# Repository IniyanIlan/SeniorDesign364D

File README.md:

# Tides of Treachery

# How to Run the Frontend
In the `src` directory, you can run:

### `npm start`

Runs the app in the development mode.\
Open [http://localhost:3000](http://localhost:3000) to view it in your browser.

The page will reload when you make changes.\
You may also see any lint errors in the console.

### `npm run build`

Builds the app for production to the `build` folder.\
It correctly bundles React in production mode and optimizes the build for the best performance.

The build is minified and the filenames include the hashes.\
Your app is ready to be deployed!

# How to Run the Backend

Split the terminal, and go to the `backend` directory.

Run this command:

### `python -m venv --system-site-packages venv`

This will create an environment with all the necessary dependencies for the application.

Next, run this command:

### `./venv/bin/activate`

This command will activate the virtual environment.

Lastly, run the backend application with this command:

### `python app.py`

# Navigate to the React Application

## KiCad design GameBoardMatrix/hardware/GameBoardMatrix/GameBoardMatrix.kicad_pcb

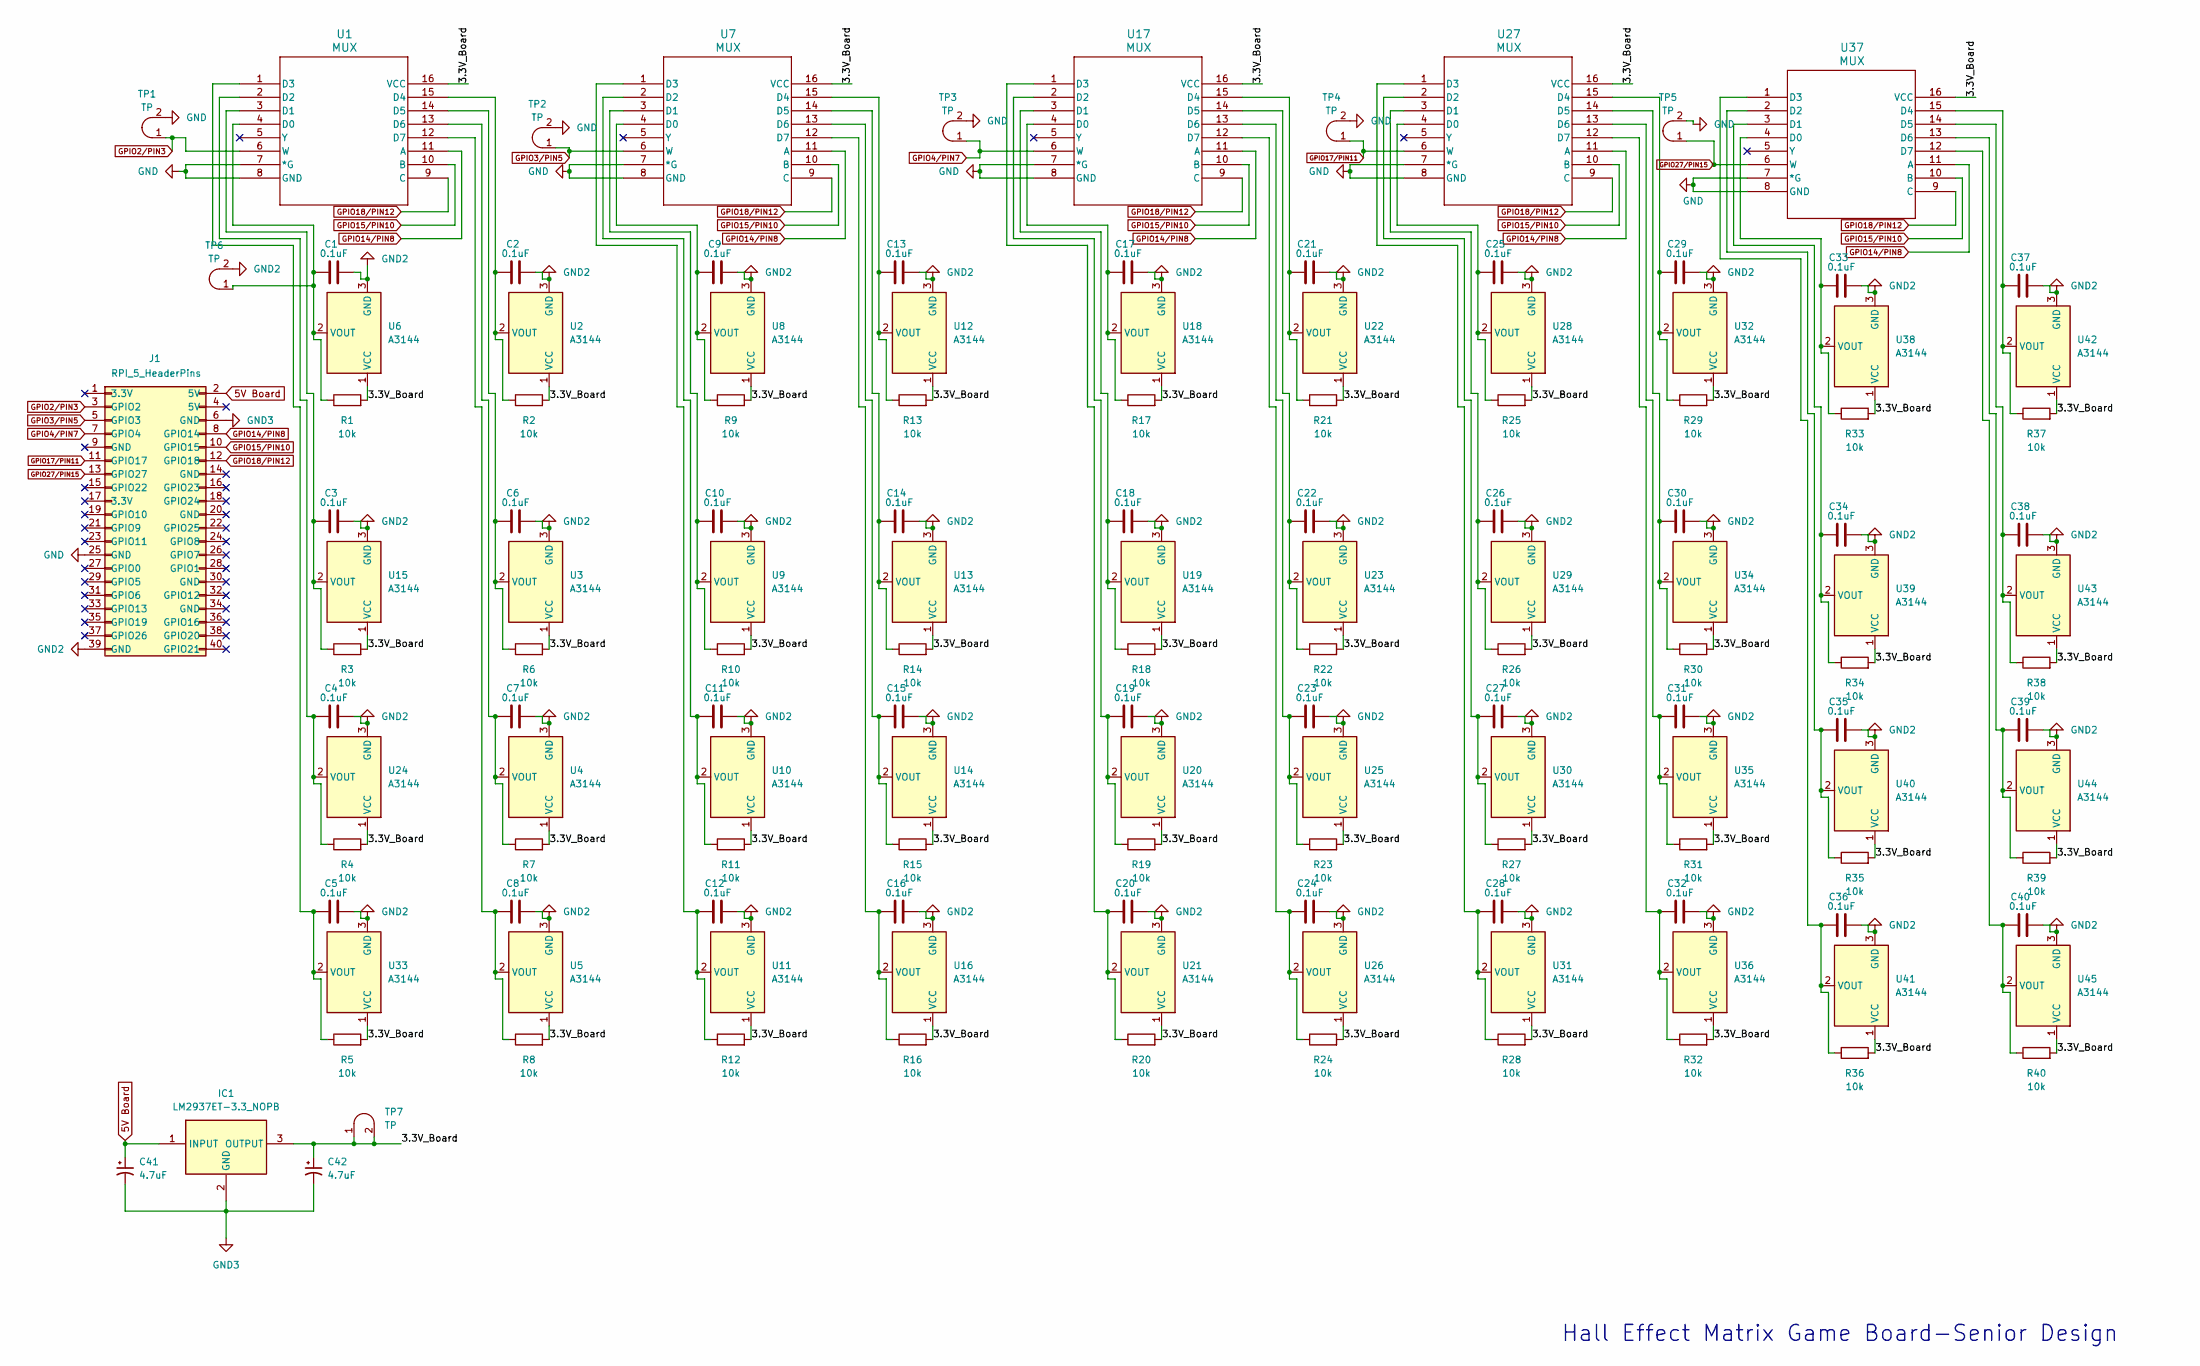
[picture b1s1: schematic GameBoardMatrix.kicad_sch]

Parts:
C1, C2, C3, C4, C5, C6, C7, C8, C9, C10, C11, C12, C13, C14, C15, C16, C17, C18, C19, C20, C21, C22, C23, C24, C25, C26, C27, C28, C29, C30, C31, C32, C33, C34, C35, C36, C37, C38, C39, C40: 0.1uF; CAP_CL21_SAM-M
C41, C42: 4.7uF; CP_Axial_L10.0mm_D4.5mm_P15.00mm_Horizontal
IC1: LM2937ET-3.3_NOPB; TO254P470X1028X1955-3P; Mouser Part Number 926-LM2937ET-3.3NOPB
J1: RPI_5_HeaderPins; PinSocket_2x20_P2.54mm_Vertical
R1, R2, R3, R4, R5, R6, R7, R8, R9, R10, R11, R12, R13, R14, R15, R16, R17, R18, R19, R20, R21, R22, R23, R24, R25, R26, R27, R28, R29, R30, R31, R32, R33, R34, R35, R36, R37, R38, R39, R40: 10k; R_Axial_DIN0204_L3.6mm_D1.6mm_P7.62mm_Horizontal
TP1, TP2, TP3, TP4, TP5, TP6, TP7: TP; Testpoint_1x02_P2.54mm
U1, U7, U17, U27, U37: MUX; D16
U2, U3, U4, U5, U6, U8, U9, U10, U11, U12, U13, U14, U15, U16, U18, U19, U20, U21, U22, U23, U24, U25, U26, U28, U29, U30, U31, U32, U33, U34, U35, U36, U38, U39, U40, U41, U42, U43, U44, U45: A3144; 1x03_P1.50mm_Vertical_A3144HallEffect

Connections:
5V Board: C41.1, IC1.1 (INPUT), J1.2 (5V)
/3.3V_Board: C42.1, IC1.3 (OUTPUT), R1.2, R2.2, R3.2, R4.2, R5.2, R6.2, R7.2, R8.2, R9.2, R10.2, R11.2, R12.2, R13.2, R14.2, R15.2, R16.2, R17.2, R18.2, R19.2, R20.2, R21.2, R22.2, R23.2, R24.2, R25.2, R26.2, R27.2, R28.2, R29.2, R30.2, R31.2, R32.2, R33.2, R34.2, R35.2, R36.2, R37.2, R38.2, R39.2, R40.2, TP7.1 (A), TP7.2 (B), U1.16 (VCC), U2.1 (VCC), U3.1 (VCC), U4.1 (VCC), U5.1 (VCC), U6.1 (VCC), U7.16 (VCC), U8.1 (VCC), U9.1 (VCC), U10.1 (VCC), U11.1 (VCC), U12.1 (VCC), U13.1 (VCC), U14.1 (VCC), U15.1 (VCC), U16.1 (VCC), U17.16 (VCC), U18.1 (VCC), U19.1 (VCC), U20.1 (VCC), U21.1 (VCC), U22.1 (VCC), U23.1 (VCC), U24.1 (VCC), U25.1 (VCC), U26.1 (VCC), U27.16 (VCC), U28.1 (VCC), U29.1 (VCC), U30.1 (VCC), U31.1 (VCC), U32.1 (VCC), U33.1 (VCC), U34.1 (VCC), U35.1 (VCC), U36.1 (VCC), U37.16 (VCC), U38.1 (VCC), U39.1 (VCC), U40.1 (VCC), U41.1 (VCC), U42.1 (VCC), U43.1 (VCC), U44.1 (VCC), U45.1 (VCC)
GND: J1.25 (GND), TP1.2 (B), TP2.2 (B), TP3.2 (B), TP4.2 (B), TP5.2 (B), U1.7 (*G), U1.8 (GND), U7.7 (*G), U7.8 (GND), U17.7 (*G), U17.8 (GND), U27.7 (*G), U27.8 (GND), U37.7 (*G), U37.8 (GND)
GND2: C1.2, C2.2, C3.2, C4.2, C5.2, C6.2, C7.2, C8.2, C9.2, C10.2, C11.2, C12.2, C13.2, C14.2, C15.2, C16.2, C17.2, C18.2, C19.2, C20.2, C21.2, C22.2, C23.2, C24.2, C25.2, C26.2, C27.2, C28.2, C29.2, C30.2, C31.2, C32.2, C33.2, C34.2, C35.2, C36.2, C37.2, C38.2, C39.2, C40.2, J1.39 (GND), TP6.2 (B), U2.3 (GND), U3.3 (GND), U4.3 (GND), U5.3 (GND), U6.3 (GND), U8.3 (GND), U9.3 (GND), U10.3 (GND), U11.3 (GND), U12.3 (GND), U13.3 (GND), U14.3 (GND), U15.3 (GND), U16.3 (GND), U18.3 (GND), U19.3 (GND), U20.3 (GND), U21.3 (GND), U22.3 (GND), U23.3 (GND), U24.3 (GND), U25.3 (GND), U26.3 (GND), U28.3 (GND), U29.3 (GND), U30.3 (GND), U31.3 (GND), U32.3 (GND), U33.3 (GND), U34.3 (GND), U35.3 (GND), U36.3 (GND), U38.3 (GND), U39.3 (GND), U40.3 (GND), U41.3 (GND), U42.3 (GND), U43.3 (GND), U44.3 (GND), U45.3 (GND)
GND3: C41.2, C42.2, IC1.2 (GND), J1.6 (GND)
GPIO2/PIN3: J1.3 (GPIO2), TP1.1 (A), U1.6 (W)
GPIO3/PIN5: J1.5 (GPIO3), TP2.1 (A), U7.6 (W)
GPIO4/PIN7: J1.7 (GPIO4), TP3.1 (A), U17.6 (W)
GPIO14/PIN8: J1.8 (GPIO14), U1.11 (A), U7.11 (A), U17.11 (A), U27.11 (A), U37.11 (A)
GPIO15/PIN10: J1.10 (GPIO15), U1.10 (B), U7.10 (B), U17.10 (B), U27.10 (B), U37.10 (B)
GPIO17/PIN11: J1.11 (GPIO17), TP4.1 (A), U27.6 (W)
GPIO18/PIN12: J1.12 (GPIO18), U1.9 (C), U7.9 (C), U17.9 (C), U27.9 (C), U37.9 (C)
GPIO27/PIN15: J1.13 (GPIO27), TP5.1 (A), U37.6 (W)
unnamed: C1.1, R1.1, TP6.1 (A), U1.4 (D0), U6.2 (VOUT)
unnamed: C3.1, R3.1, U1.3 (D1), U15.2 (VOUT)
unnamed: C4.1, R4.1, U1.2 (D2), U24.2 (VOUT)
unnamed: C5.1, R5.1, U1.1 (D3), U33.2 (VOUT)
unnamed: C2.1, R2.1, U1.15 (D4), U2.2 (VOUT)
unnamed: C6.1, R6.1, U1.14 (D5), U3.2 (VOUT)
unnamed: C7.1, R7.1, U1.13 (D6), U4.2 (VOUT)
unnamed: C8.1, R8.1, U1.12 (D7), U5.2 (VOUT)
unnamed: C9.1, R9.1, U7.4 (D0), U8.2 (VOUT)
unnamed: C10.1, R10.1, U7.3 (D1), U9.2 (VOUT)
unnamed: C11.1, R11.1, U7.2 (D2), U10.2 (VOUT)
unnamed: C12.1, R12.1, U7.1 (D3), U11.2 (VOUT)
unnamed: C13.1, R13.1, U7.15 (D4), U12.2 (VOUT)
unnamed: C14.1, R14.1, U7.14 (D5), U13.2 (VOUT)
unnamed: C15.1, R15.1, U7.13 (D6), U14.2 (VOUT)
unnamed: C16.1, R16.1, U7.12 (D7), U16.2 (VOUT)
unnamed: C17.1, R17.1, U17.4 (D0), U18.2 (VOUT)
unnamed: C18.1, R18.1, U17.3 (D1), U19.2 (VOUT)
unnamed: C19.1, R19.1, U17.2 (D2), U20.2 (VOUT)
unnamed: C20.1, R20.1, U17.1 (D3), U21.2 (VOUT)
unnamed: C21.1, R21.1, U17.15 (D4), U22.2 (VOUT)
unnamed: C22.1, R22.1, U17.14 (D5), U23.2 (VOUT)
unnamed: C23.1, R23.1, U17.13 (D6), U25.2 (VOUT)
unnamed: C24.1, R24.1, U17.12 (D7), U26.2 (VOUT)
unnamed: C25.1, R25.1, U27.4 (D0), U28.2 (VOUT)
unnamed: C26.1, R26.1, U27.3 (D1), U29.2 (VOUT)
unnamed: C27.1, R27.1, U27.2 (D2), U30.2 (VOUT)
unnamed: C28.1, R28.1, U27.1 (D3), U31.2 (VOUT)
unnamed: C29.1, R29.1, U27.15 (D4), U32.2 (VOUT)
unnamed: C30.1, R30.1, U27.14 (D5), U34.2 (VOUT)
unnamed: C31.1, R31.1, U27.13 (D6), U35.2 (VOUT)
unnamed: C32.1, R32.1, U27.12 (D7), U36.2 (VOUT)
unnamed: C33.1, R33.1, U37.4 (D0), U38.2 (VOUT)
unnamed: C34.1, R34.1, U37.3 (D1), U39.2 (VOUT)
unnamed: C35.1, R35.1, U37.2 (D2), U40.2 (VOUT)
unnamed: C36.1, R36.1, U37.1 (D3), U41.2 (VOUT)
unnamed: C37.1, R37.1, U37.15 (D4), U42.2 (VOUT)
unnamed: C38.1, R38.1, U37.14 (D5), U43.2 (VOUT)
unnamed: C39.1, R39.1, U37.13 (D6), U44.2 (VOUT)
unnamed: C40.1, R40.1, U37.12 (D7), U45.2 (VOUT)

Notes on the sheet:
Hall Effect Matrix Game Board-Senior Design

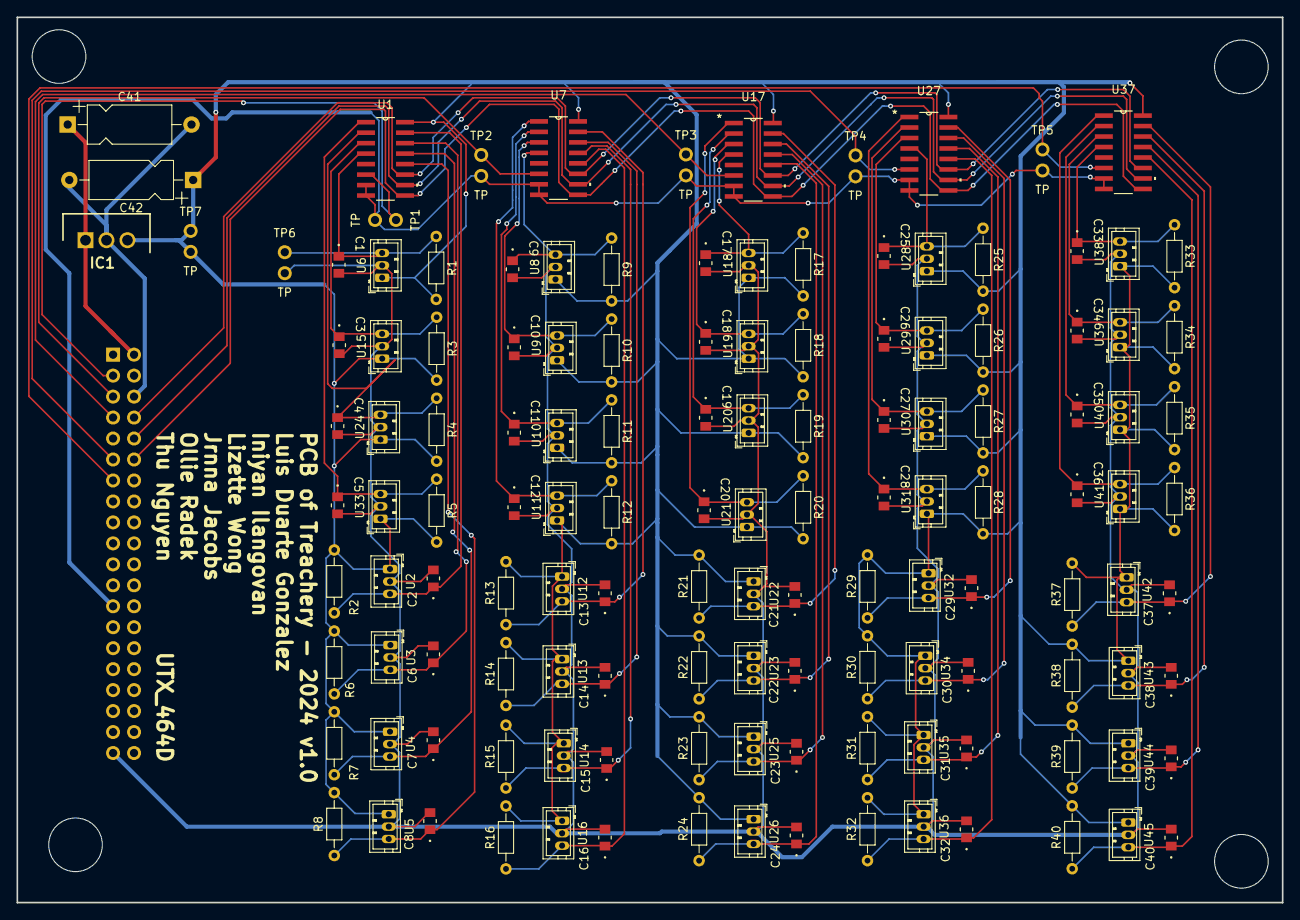
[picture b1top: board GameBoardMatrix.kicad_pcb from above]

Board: 2 copper layers, 153.3 x 107.2 mm, 136 parts (1 on the bottom side), 53 nets.

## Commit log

2024-02-14 Updating our README.md
2024-02-14 Added some barebones edits to our page
2024-02-14 Revised README
2024-03-29 Creating React app and organizing Pages/ and CSS/
2024-04-12 First Update for Home Page and User Name Entry
2024-04-13 Adding page for the game
2024-04-13 Adding content to Leaderboard and adjusting player size
2024-04-17 removed node_modules
2024-04-17 excavation functionality added
2024-04-17 Making minor tweaks to the leaderboard
2024-04-17 Updated Code for Risk Reduction
2024-04-17 Added Dice Reading Files
    Dark and Light faces
2024-04-17 Resolving a merge conflict
2024-09-26 flask skeleton created
2024-09-27 testing commit
2024-09-30 updated project structure
2024-09-30 fix: renaming Dice Reading directory
2024-10-02 feature: adding test rpi5 camera code
2024-10-02 Documenting failed Risk Reduction stuff
2024-10-02 Revert "Documenting failed Risk Reduction stuff"
    This reverts commit aaf828f8b6b9af9823b3dcc0a18363277fb864b0.
2024-10-03 Creating a page to enter number of players
2024-10-04 first push, creating initial python file
2024-10-08 added initial action logic
2024-10-09 feature: chaging UI for figma, buttons added, leaderboard needs work
2024-10-09 More changes
2024-10-09 fix: resolving CSS problem
2024-10-09 added rpi compatability
2024-10-09 Added GPIO Test file
2024-10-10 feature: adding dice work from hardware team
2024-10-11 Move Game.css and Game.js to Tracking folder
2024-10-11 Modifying the UI for SettingUp pages
2024-10-11 UI Modifying
2024-10-11 Changed gpio test stuff
2024-10-11 Dice Reader commpatible with RPI 5
2024-10-12 Finished GPIO testing
2024-10-13 Started on Matrix testing
2024-10-13 fix: Leaderboard adjustable with proper spacing
2024-10-14 Adding to tests
2024-10-14 Finished matrix test code, added datasheet resource folder
2024-10-14 feature: adding the Trigger Dice button for demo
2024-10-14 tried to update navigation for excavation pages
2024-10-14 final Matrix test
2024-10-14 adding flask support
2024-10-14 excavation logic sort of works
2024-10-14 excavation logic finally works
2024-10-14 fix: resolving app.py for trigger
2024-10-14 started attack
2024-10-14 mid demo it works
2024-10-16 Created schematic/pcb project
2024-10-18 Having fun with multiprocessing :)
2024-10-18 Finished example multiprocessing
2024-10-18 updating
2024-10-19 bruh
2024-10-19 bruh v2
2024-10-23 feature: adding shared memory for flags and data
2024-10-23 Added shutdown/freeing
2024-10-28 Started on PCB/Schematic Design
2024-10-30 Finished most of the schematic
    Still need to tie outputs to gpio pins
2024-10-31 some UI changes to game page
2024-11-01 updated UI and fixed logic for attacking and chest list
2024-11-02 I no like camra :(
2024-11-03 Turn-Tracking feature
2024-11-04 %50 done with PCB
2024-11-05 duck
2024-11-06 Score-Tracking feature and Leaderboard
2024-11-06 Added order details
2024-11-06 Matrix shared memory done, must pair with rpi5 now
2024-11-06 Fix: increasing sampling amount for dice reading code
2024-11-07 excavate treasure works
2024-11-07 Implemented Winning Condition and Winner page
2024-11-08 updated excavation
2024-11-08 Added present and past matrices
2024-11-08 feature: adding action functionality, couple of other changes
2024-11-08 fleshed out matrix code
2024-11-09 attack and excavate button worked, but then i puled luis's code and now attack doesn't redirect but it works behind the scenes
2024-11-10 attack button works with proper json response
2024-11-10 attack function now successfully adds and removes from each player's gold
2024-11-10 excavate bomb should now deduct gold if the player runs out of attempts
2024-11-10 Gonna switch to Pi so I have to push
2024-11-10 Sail and player setup done
2024-11-11 deleted one file which was not nessacary
2024-11-11 feature: adding more stuff
2024-11-11 fix: fixing demo bugs
2024-11-13 some ui fixes
2024-11-13 fix: bug fixes and more
2024-11-13 fix: adding delays, attack and excavate buttons working better
2024-11-15 Adding background music and sound effect for buttons
2024-11-15 feature: script starting, dice bugs fixed, other stuff:
2024-11-15 Optimized Dice Reader Code
2024-11-18 post playtest1 update 1
2024-11-18 post playtest 1 update 2
2024-11-18 slightly changed some shared memory stuff
2024-11-21 pushing for the day
2024-11-28 Pushing Pi code
2024-11-30 updated time out messages, attack screen UI, increase attack reward, randomize chests, updated text and gold distrubution
2024-12-01 color selection and removed debugging add 100 gold buttons
2024-12-01 Wrote hex board to hall effect mappings
2024-12-01 BFS Tested
2024-12-02 fix: adding roll dice to turn tracking, other fixes, pcbtest
2024-12-04 Neopixels for you ungrateful animals
2024-12-04 jk ily <3
2024-12-04 feature: adding hexagon mapping for the chests
2024-12-05 the motion of the ocean
2024-12-05 added boom boom
2024-12-06 Adding background music and boom sound effect
2024-12-06 features: bunch of changes to frontend and adding LED capabilities
2024-12-06 fix: adding some fixes to Turntracking and Excavate Treasure
2024-12-06 Adding gold sound effect
2024-12-06 Adding winner sound
2024-12-07 fixed UI, disabled attack and excavate buttons when not in use
2024-12-07 feature: we got LED working?
2024-12-08 fix: led fixes
2024-12-08 Added some functionality with sail
2024-12-09 Adding fighting sound effect
